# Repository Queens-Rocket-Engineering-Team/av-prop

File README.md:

# Propulsion Integration Systems
> 2025-2026 Season - Propulsion Integration Projects

> [!IMPORTANT]
> Make sure to initialize and pull the repository's git submodules to acquire all schematic library and board design dependencies:
> ```bash
> git submodule update --init --recursive
> ```

- Repository contains Avionics schematics, PCBs, and firmware for integrating with the propulsion stack.

### Folder Structure
- [`/Schematics`](./Schematics/) : Electrical design files (KiCad V8)  
- [`/Firmware`](./Firmware/) : C/C++ Code
- [`/Datasheets`](./Datasheets/) : Datasheets and reference materials  

### Documentation
- Boards and code are documented through `README` files in their respective directories. 

### Usage 
- To add or update features and work on new projects, create a new branch. 
- For **PCB** projects, name the branch with the convention: `pcb/board-name` or `pcb/board-feature` for updates.
- For **firmware** projects, name the branch with the convention: `fw/project-name` or `fw/project-feature` for updates.

--- 

QRET Avionics 25/26

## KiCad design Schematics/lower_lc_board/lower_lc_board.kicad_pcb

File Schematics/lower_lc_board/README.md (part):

# Lower Control Board (HYDRA) Documentation

<!--- removed left align div - weird github web issue --->
<details>
<summary><strong>Table of Contents</strong></summary>
  
- [Lower Control Board (HYDRA) Documentation](#lower-control-board-hydra-documentation)
  - [Overview](#overview)
    - [Key Features](#key-features)
  - [Circuit Design](#circuit-design)
    - [Power Management](#power-management)
      - [Power Entry](#power-entry)
      - [Power MUX](#power-mux)
      - [Power Switching](#power-switching)
    - [MCU Breakout](#mcu-breakout)
      - [Mode Selection](#mode-selection)
      - [Flash Storage Module](#flash-storage-module)
      - [CANBUS Interface](#canbus-interface)
      - [Serial Wire Debug](#serial-wire-debug)
      - [USB Interface](#usb-interface)
      - [System Feedback](#system-feedback)
    - [Valve Control](#valve-control)
    - [Sensing](#sensing)
      - [Data Acquisition](#data-acquisition)
      - [Pressure Transducers](#pressure-transducers)
      - [Thermocouples](#thermocouples)
  - [Board Design](#board-design)
    - [Physical Design Notes](#physical-design-notes)
    - [Electrical Characteristics](#electrical-characteristics)
    - [System Partitioning](#system-partitioning)
  - [Revision History](#revision-history)
  - [Contributors](#contributors)

</details>

---

## Overview

<div style="display: flex; gap: 10px;">

</div>

<em>Fig. 1: Hydra</em>

The **Lower LC/Hydra** board is a control board designed for integration with the rocket's propulsion system.
It operates in the **lower valve bay**, and drives solenoids to control the **dump** and **fill** valves.
This board supports analog pressure and temperature sensing, two digital hall-effect sensors for solenoid-status reading, and communication with the rest of the stack through CANbus.

Interfaces with:
- STM32F1 MCU
- Two 24V 205292 Solenoids
- Two 24V 4-20mA Pressure Transducers (PT)
- An Omega SA3-K Thermocouple (TC)
- Two TMAG273 digital hall-effect sensors (via breakout board)

### Key Features

- STM32F1 microcontroller with additional memory
- I2C and SPI interfaces for sensor integration
- Controlled power delivery for sensors and solenoids
- ORing circuits for power management
- Visual indication for status and debugging
- 4-layer PCB with dedicated ground planes
- Protection and filtering components across board

---

## Circuit Design

This board is primarily composed of four circuit modules representing its critical systems: [Power Management](#power-management), [STM32 Breakout](#mcu-breakout), [Valve Control](#valve-control), and [Sensing](#sensing).

All schematics are available as `kicad_sch` files in this directory.

---

### Power Management

This board receives power from the Hybrid Power Module through the Backplane.
For more information on power delivery, check out [this repository](https://github.com/Queens-Rocket-Engineering-Team/av-power).

The supply delivers **three** levels of voltage to the board:

| Voltage (V) | Purpose |
|-------------|---------|
| 3.3 | Logic supply for microcontroller and other peripheral devices; also serves as a reference for signal conditioning and protection circuits |
| 5 | Intermediate supply for specific peripheral devices |
| 24 | High-voltage supply for driving external devices such as solenoids and sensors |

> **Note:** 3.3V is referred to as **3V3** throughout this document.

#### Power Entry

Power rails enter through a Molex Micro-Fit connector and are conditioned by bulk filtering and input protection circuitry. These circuits apply to the 5V and 24V rails, each decoupled with 100 µF electrolytic capacitors to handle voltage transients and provide local energy storage. The 24V rail includes a 2A fuse for overcurrent protection.

Other power sources come from communication devices such as the USB connection and the JTAG debugger. The USB creates a voltage rail of 5V, which is then stepped down to 3V3 with a **Low-Dropout Regulator (LDO)**. The JTAG debugger supplies 3V3.

All rails feature test points and LEDs for diagnosis and debugging.

#### Power MUX

Power Multiplexers (MUX) are circuits that select between multiple power inputs to drive a single load. This is needed to avoid back-feeding between power sources, which could lead to unintended powering of interfaces and potential damage.

This implementation uses a **Triple OR-ing** circuit to select between three 3.3V inputs: Backplane (V_BP), JTAG (V_SWD), and USB (V_USB).

- The circuit involves three Ideal Diode ICs, which use a MOSFET and controller to mimic the behaviour of an **Ideal Diode** (zero voltage drop when forward-biased, zero current when reverse-biased).
- The logic follows:
  - **ON condition**: A chip turns on if its *Vin* is **higher** than the common output rail *Vout*.
  - Each chip uses its enable *CE* pin to monitor the output rail; if it sees a higher voltage present, it remains closed to prevent back-feeding.

In summary, a source will only drive the load if its voltage is higher than the current voltage on the output rail, allowing only **one** source to drive the output rail at a time.

- Capacitors are placed at the input pins to filter noise and prevent voltage spikes when a source is suddenly connected or disconnected.
- On the output rail, capacitors act as reservoirs to maintain steady voltage while also filtering noise generated by the loads connected to the 3V3 rail.

#### Power Switching

The delivery of 24V to the pressure transducers and solenoids is controlled through a switching circuit.

- For PTs, this was added to reduce power consumption by enabling sensor power only during active operation.
- For solenoids, this was added as a pre-actuation layer to provide additional protection and controlled switching.
- The controlled output rails are identified as `VPT` and `VSOL` respectively.

The circuit uses a **CMOS** (dual-MOSFET) setup: one N-channel at the input to drive a P-channel for the output.

**MOSFET Basics**

| Type | ON Condition |
|------|-------------|
| N-Channel | Gate voltage higher than source -> V<sub>GS</sub> > V<sub>th</sub> |
| P-Channel | Gate voltage lower than source -> V<sub>GS</sub> < V<sub>th</sub> |

The **ON** state connects the **Drain** (output) pin to the **Source** pin.

**Logic**

- The STM32 outputs a digital signal to drive the gate of the N-channel MOSFET. The source of the MOSFET is set to GND (0V).
- The gate is now at a higher voltage than the source, setting the drain to GND.
- The drain connects to a resistor divider with 24V to drive the gate of the P-channel MOSFET. The source of the MOSFET is set to 24V.
  - The resistor divider limits the gate voltage to approximately 14.81 V, lower than the source, setting the drain to 24V and powering the output rail.

$$V_g = 24 \times \frac{10k}{(6.2k + 10k)} \approx 14.81\ \text{V}$$

$$V_{gs} = 14.81 - 24 \approx -9.19\ \text{V}$$

> From the [DMP4065 Datasheet](${KIPRJMOD}/../../Datasheets/pMOSFET_DMP4065S-7_DS.pdf), V<sub>GS(max)</sub> = ±20 V, within safe operating range.

- `VPT` is filtered using a Pi filter with a ferrite bead between a 10 µF bulk capacitor and a 0.1 µF decoupling capacitor to reduce ripple and high-frequency noise.
- `VSOL` is decoupled with a 100 µF electrolytic capacitor for local energy storage and transient support.
- `VSOL` also uses a voltage divider for sensing. Two resistors (100 kΩ and 10 kΩ) scale the 24V input down to approx. 2.18V for measurement by an STM32 ADC input:

$$V = 24 \times \frac{10k}{(100k + 10k)} \approx 2.18\ \text{V}$$

The circuit also includes two resistors at the MOSFET gate:
- **Series (Gate) Resistor**: Limits inrush current into the gate while controlling switching speed and protecting the MCU pin.
- **Pull-Down Resistor**: Connects signal to GND to define a default logic state when nothing is actively driving the gate.

---

### MCU Breakout

The [STM32F103](https://www.st.com/resource/en/datasheet/stm32f103cb.pdf) was selected for this board's MCU.

Key features:
- 72 MHz ARM Cortex-M3 core
- Internal CAN controller
- Compact LQFP48 package

#### Mode Selection

The STM32 can be put into **BOOT** mode and **RESET** with onboard buttons.

**BOOT** mode determines whether the chip runs existing code from flash memory or waits to download new firmware.
- The STM32 reads the state of the BOOT pin (BOOT0) during reset to select the appropriate boot mode.
- It is **active-high**: when pulled HIGH (3V3), it will wait for new code over serial/USB.
- The circuit consists of a momentary push-button and a pull-down resistor to ensure the chip is disabled by default. A second BOOT pin (BOOT1) is pulled low to prevent entering SRAM mode.

**RESET** controls the Reset (NRST) pin --- the ON/OFF switch for the STM32.
- It is **active-low**: when pulled to GND the chip turns off; when released, it restarts.
- The circuit consists of a momentary push-button, a pull-up resistor to ensure the chip is enabled by default, and a 0.1 µF capacitor to filter out button noise (debouncing).

| BOOT0 Level | Boot Mode |
|-------------|-----------|
| HIGH | Programming Mode |
| LOW | Memory Mode |

#### Flash Storage Module

This board includes a BY25Q12BE5 SPI flash memory module providing 16 MB of external non-volatile storage, connected to the MCU via an SPI interface (SCLK, MOSI, MISO, CS).

#### CANBUS Interface

The STM32 includes an internal CAN controller but requires a CAN transceiver to interface with the stack's CANBUS.
- Differential pairs from the backplane edge connector are routed to the CAN transceiver, which converts them into TX and RX signals for the STM32.
- The CAN transceiver selected is a high-speed [TCAN1051](https://www.ti.com/lit/ds/symlink/tcan1051h.pdf).

#### Serial Wire Debug

This board supports Serial Wire Debug (SWD) for programming and debugging the MCU using an ST-Link debugger.
- The SWD interface uses dedicated SWDIO and SWCLK lines routed to a debug header.
- This enables flashing and debugging via an ST-Link programmer.

#### USB Interface

The STM32 interfaces with USB via a CP2102N USB-to-UART bridge.
- USB differential pairs are routed directly to the CP2102N, which converts them to UART signals for the STM32.
- The STM32 communicates with the bridge using standard TX and RX lines.

#### System Feedback

This board incorporates feedback through LEDs:
- Visual indicators include a DEBUG indicator, CAN status, and a general STATUS indicator.
- These consist of standard current-driven LEDs and an ARGB LED.

---

### Valve Control

Valves are actuated via solenoids using MOSFET-based switching circuits driven by the MCU.
- The system uses two Festo 205292 solenoids to control the rocket's dump and fill valves.
  - Operates at 24V and is active-low.
  - Controlled via low-side switching (active when pulled to ground).
  - Interfaces through a MOLEX Nano-Fit connector.

The circuits consist of an N-channel MOSFET for low-side switching, flyback (Schottky) diodes for protection, and hardware-driven LEDs for visual indication.

> See the **MOSFET Basics** section under [Power Management](#power-management) for background on MOSFET operation.

**Logic**

- The solenoid positive terminal is connected to 24V.
- The STM32 outputs a digital signal that serves as the circuit's control input.
- This signal feeds an N-channel MOSFET with its source connected to GND (0V) and its drain connected to the negative terminal of the solenoid (SOL_RET).
- The signal turns the MOSFET `ON` since the gate voltage (3.3V) is higher than the source voltage (0V).
- This connects the MOSFET drain to source, pulling the solenoid negative terminal to ground and actuating the valve.

**Protection & Filtering**

- A 40V, 3A SS34 Schottky diode is placed across the solenoid to provide a path for inductive flyback current during turn-off, protecting against voltage spikes generated by inductive loads during switching.
- A local 0.1 µF capacitor is placed near the connector for high-frequency decoupling.

**Visual Indication**

- A purely hardware-driven LED circuit provides indication and debugging.
  - An LED with a series current-limiting resistor is placed across the solenoid, with the anode on the positive terminal and the cathode on the negative terminal.
  - By default, the anode is connected to 24V and the cathode is floating.
  - When the solenoid is driven and the negative terminal is pulled low, the LED is connected on both sides and emits.

---

### Sensing

This board interfaces with several external sensors, including analog pressure transducers, thermocouples, and digital hall-effect sensors.
- Pressure transducers are used for analog telemetry measurements.
- Hall-effect sensors are used for solenoid state detection and feedback.

#### Data Acquisition

Analog sensor data is acquired via an external **ADC** (Analog-to-Digital Converter) through the SPI protocol. Digital signals from hall-effect sensors are acquired through the I2C protocol.

The ADC used is the [ADS131M04](https://www.ti.com/lit/ds/symlink/ads131m04.pdf): 8 input channels, 24-bit resolution, 32 kSPS programmable sampling rate.
- Each input channel receives a voltage or differential voltage from a sensor (V<sub>ref</sub> = 1.2 V).
- A [delta-sigma](https://e2e.ti.com/blogs_/archives/b/precisionhub/posts/delta-sigma-adc-basics-understanding-the-delta-sigma-modulator) modulator converts the voltage into a high-frequency bitstream representing the input analog signal. This modulator is driven by an external crystal oscillator (8.319 MHz).
- The bitstream is then filtered to produce a clean, high-resolution digital value.
- The ADC sends a 24-bit number representing the measured voltage to the MCU via SPI.

An **RC filter** is used at the ADC inputs as a low-pass filter to smooth out high-frequency noise. The capacitor charges and discharges through the resistor, smoothing fast transients so the ADC sees a stable voltage.

> **Brief Overview on Analog Signals:** Analog signals vary continuously, taking any value within a given range, unlike digital signals which have discrete levels. Changes in a sensor's physical quantity are represented proportionally as a voltage or current signal.

#### Pressure Transducers

The PT circuits are built around signal conditioning and protection before the ADC.
- The PT used is a 4-20 mA [Setra 209H](https://www.setra.com/hubfs/Setra_Product_Data_Sheets/Model_209H_Spec_Sheet_2016_PRELIMINARY_WATERMARK.pdf) connected via Molex Nano-Fit.
- The signal line is initially referenced to GND through a 62 Ω shunt resistor to produce a voltage drop proportionate to the signal (current):

$$R_{shunt} = \frac{V_{ref}}{I_{max}} = \frac{1.2\ \text{V}}{0.02\ \text{A}} = 60\ \Omega$$

> A 62 Ω resistor was chosen for availability.

- The signal is then clamped to 3.3V and GND using low-leakage diodes.
- A 1 kΩ resistor is placed in series between the signal and diode to limit current into the diodes during overvoltage conditions.
- The clamped signal then passes through a 200 Ω resistor and 10 nF capacitor, forming the RC low-pass filter before being sampled by the ADC.

#### Thermocouples

The TC circuits are built around signal conditioning, protection, and transformation before the ADC.
- The TC used is an [Omega SA3-L](https://assets.omega.com/pdf/test-and-measurement-equipment/temperature/sensors/thermocouple-probes/SA3.pdf) connected via screw terminal.
- Unlike the 4–20 mA pressure transducer, it produces a small differential voltage across its two output wires, so the device uses two signal inputs for differential measurement.
- Both signal lines are resistor-biased with two 1 MΩ resistors, connected to 3V3 and GND respectively, to establish a defined reference operating point and prevent floating inputs.
- The signals are then clamped to 3.3V and GND using low-leakage diodes.
- A 1 kΩ resistor is placed in series between each signal and diode to limit current during overvoltage conditions.
- Each signal then passes through a 200 Ω resistor and 10 nF capacitor, forming the RC low-pass filter before being sampled by the ADC.

**Cold-Junction Compensation**

Cold-junction compensation is used to determine the true absolute temperature at the TC connector, since a thermocouple only measures the temperature difference between the measurement junction and the reference junction.

- A **thermistor** placed as close as possible to the TC screw terminal measures the reference junction (PCB terminal) temperature.
- The thermistor uses a voltage divider to produce a proportional signal for processing by the STM32's internal ADC.

---

## Board Design

### Physical Design Notes

- The board measures 69.5 mm × 60 mm.
- Connectors are placed at the board edge for accessibility.
- The board outline deviates from the standard avionics form factor to fit the lower valve bay.
- A side-mounted Molex connector is used instead of the standard edge-connector (PCIe) connector for power and CAN entry due to space constraints.

### Electrical Characteristics

The board is a 4-layer PCB with dedicated ground planes for noise reduction and signal integrity.

| Layer | Net | Purpose |
|-------|-----|---------|
| 1 | Signals + Power | Top-level routing |
| 2 | GND | Inner ground plane |
| 3 | GND | Inner ground plane |
| 4 | Signals + Power | Bottom-level routing |

- Inner ground planes minimize impedance in return paths and reduce EMI.
- Decoupling capacitors are placed close to IC power pins to reduce loop inductance.
- Valve control circuits use local ground pours to support high-current return paths (MOSFET source).

### System Partitioning

- The board is partitioned into distinct analog, digital, and power domains to reduce noise coupling and improve signal integrity.
- Analog sensing circuitry is physically isolated from high-current valve control circuits.
- Power distribution is routed from the top of the board and propagates downward through regulated domains.
- High-current switching paths are separated from sensitive signal routing to minimize interference.

---

## Revision History

| Revision | Date | Description |
|----------|------|-------------|
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
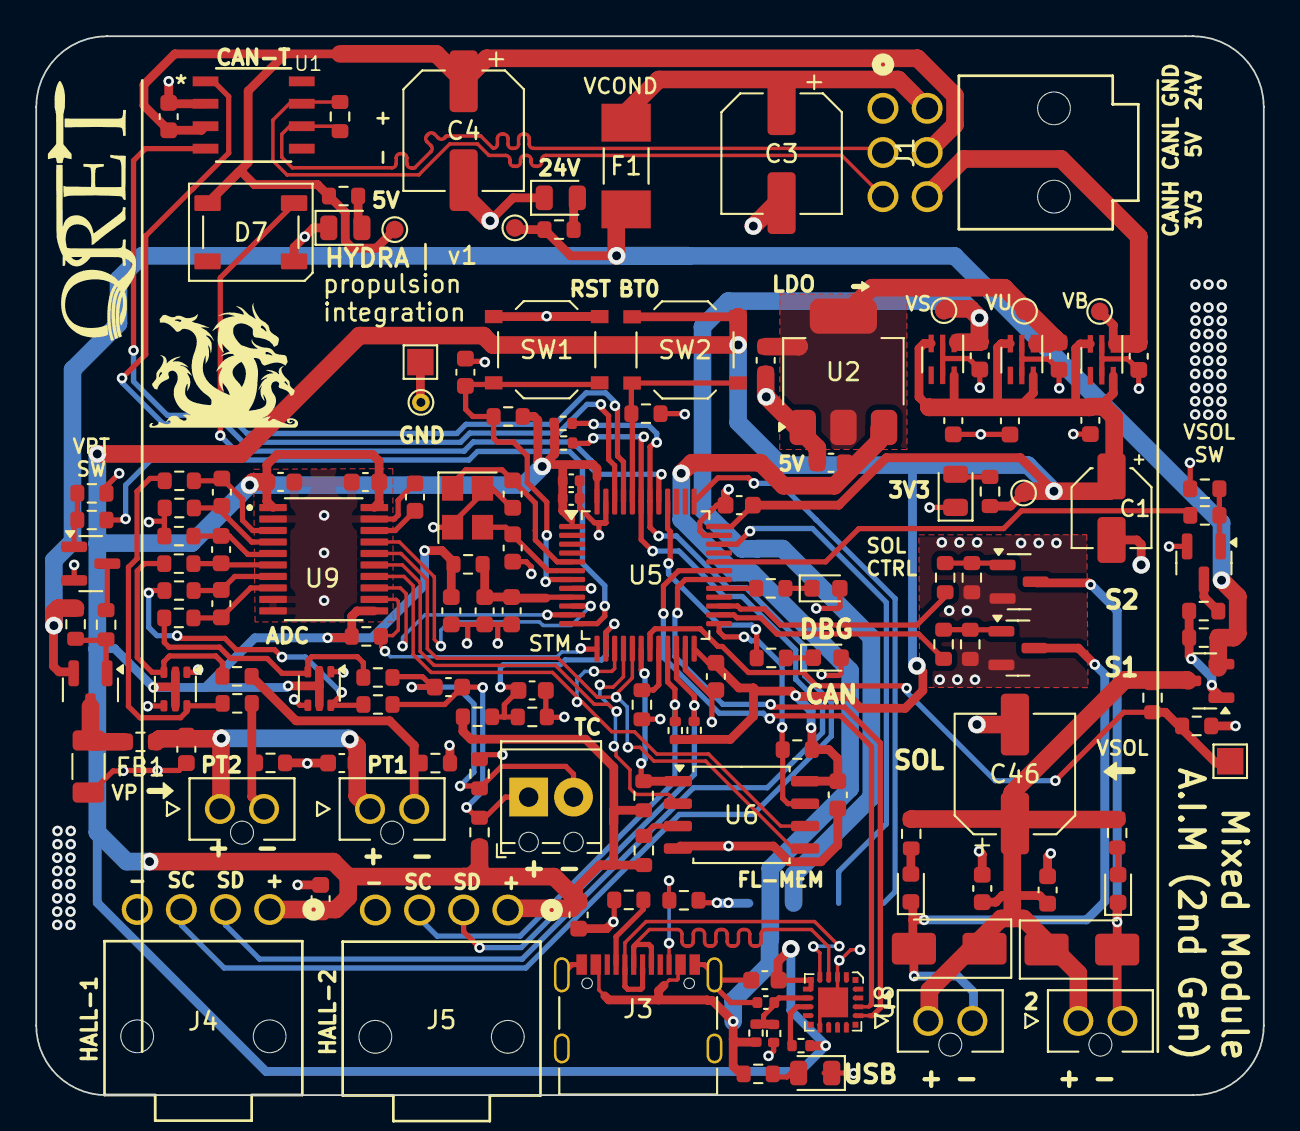
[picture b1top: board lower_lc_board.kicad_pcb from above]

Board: 4 copper layers, 69.5 x 60.0 mm, 149 parts (1 on the bottom side), 86 nets.

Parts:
C1: 10uF; CP_Elec_4x5.4
C2, C18, C23, C30, C33, C39, C41, C45, C52: 0.1uF; C_0603_1608Metric
C3, C4, C46: 100uF; CP_Elec_6.3x5.9
C5, C6, C28, C43, C44, C48, C49: 1uF; C_0603_1608Metric
C7, C12, C21, C50: 10uF; C_0603_1608Metric
C8, C9, C17: 100nF; C_0603_1608Metric
C10, C11: 10p; C_0603_1608Metric
C13, C14: 100n; C_0402_1005Metric
C15, C16: 100n; C_0603_1608Metric
C20: 1uF; C_0402_1005Metric
C26, C27, C34, C56: 10nF; C_0603_1608Metric
C29: 220 nF; C_0603_1608Metric
C35: 10uF; C_1206_3216Metric
C51: 1nF; C_0603_1608Metric
D1: PWR_3V3_LED (GRN); LED_0805_2012Metric
D2: PWR_24V_LED (GRN); LED_0805_2012Metric
D3: PWR_5V_LED (GRN); LED_0805_2012Metric
D4: USB_LED (GRN); LED_0805_2012Metric
D5: DB_LED (YLW); LED_0603_1608Metric
D6: CAN_LED (WHT); LED_0603_1608Metric
D7: SYS_LED; LED_WS2812B_PLCC4_5.0x5.0mm_P3.2mm
D11: SOL2_LED (YELW); LED_0603_1608Metric
D12: SOL1_LED (YELW); LED_0603_1608Metric
D13, D18: BAV199DW; SOT-363_SC-70-6
D15, D16: SS34; D_SMA
F1: Fuse; FUSC6125X279N
FB1, FB2: 600R; R_0603_1608Metric
J1: Conn_01x06; CONN_SD-105314-100_06_MOL
J2: SWD_CONN; SWD_PinHeader_1x04_P2.54mm_Horizontal_SMD
J3: USB_C_CONN; USB_C_DB-108PWB
J4: HALL-1; CONN_SD-105313-100_04_MOL
J5: HALL-2; CONN_SD-105313-100_04_MOL
J6, J8: PT; MOLEX_1053091102
J7: Screw_Terminal_01x02; TerminalBlock_Phoenix_MPT-0,5-2-2.54_1x02_P2.54mm_Horizontal
J9, J10: SOL_CONN; MOLEX_1053091102
Q1, Q2: AO3400A; SOT-23
Q3, Q5: 2N7002; SOT-23
R1: 3.3k; R_0603_1608Metric
R2, R30, R31: 12k; R_0603_1608Metric
R3, R16, R23, R51: 6.2k; R_0603_1608Metric
R5, R6, R7, R8, R22, R25, R43, R48, R49, R50, R52, R54, R60: 10k; R_0603_1608Metric
R9, R10: 5.1k; R_0603_1608Metric
R11: 22k; R_0402_1005Metric
R12: 47k; R_0402_1005Metric
R13: 1k; R_0402_1005Metric
R14: 680; R_0603_1608Metric
R15: 270; R_0603_1608Metric
R17, R18, R21, R45: 2.2k; R_0402_1005Metric
R19, R20: 1.2k; R_0603_1608Metric
R24, R28, R33, R37: 1k; R_0603_1608Metric
R26, R27: 1M; R_0603_1608Metric
R29, R34, R36, R38, R40, R41, R44, R53: 200; R_0603_1608Metric
R32, R35: 62; R_0603_1608Metric
R39, R42, R47: 100k; R_0603_1608Metric
R46: 120; R_0603_1608Metric
SW1: SW_STM_RESET; SW_Push_1P1T_XKB_TS-1187A
SW2: SW_STM_BOOT_MODE; SW_Push_1P1T_XKB_TS-1187A
TH1: Thermistor; R_0603_1608Metric
TP1: 24V-TP; TestPoint_Pad_D1.0mm
TP2: 3V3-TP; TestPoint_Pad_D1.0mm
TP3: GND-TP-H; TestPoint_THTPad_D1.0mm_Drill0.5mm
TP4: 3V3_BP; TestPoint_Pad_D1.0mm
TP5: GND-TP-P; TestPoint_Pad_1.5x1.5mm
TP6: 3V3_USB; TestPoint_Pad_D1.0mm
TP7: VSOL.S; TestPoint_Pad_1.5x1.5mm
TP9: V_SWD_TP; TestPoint_Pad_D1.0mm
TP13: 5V-TP; TestPoint_Pad_D1.0mm
U1: TCAN1051HGVDR; SOIC_1044BDR_TEX
U2: AMS1117-3.3; SOT-223-3_TabPin2
U3, U4, U10: ID_LM66100DCKR; SC-70-6
U5: STM32F103CBT6; LQFP-48_7x7mm_P0.5mm
U6: BY25Q128ES; SOIC-8_5.23x5.23mm_P1.27mm
U8: CP2102N-Axx-xQFN20; QFN-20-1EP_3x3mm
U9: ADC_ADS131M04IPWR; SOP65P640X120-20N
U11, U12: DMP4065S-7; SOT-23
Y1: X322516MMB4SI; Crystal_SMD_3225-4Pin_3.2x2.5mm

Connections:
5V_USB: C7.1, J3.A4 (VBUS), J3.A9 (VBUS), J3.B4 (VBUS), J3.B9 (VBUS), R11.2, R16.1, U2.3 (VI)
+3.3VA: C45.2, C48.2, FB2.1, U5.9 (VDDA)
+3V3: C1.1, C13.1, C14.1, C15.1, C16.1, C17.1, C21.2, C23.1, C28.2, C30.2, C33.1, C43.2, C49.1, C50.1, C51.1, C52.1, D13.2 (K2), D13.5 (K4), D18.2 (K2), D18.5 (K4), FB2.2, J4.1, J5.1, J7.1, R1.1, R6.2, R7.2, R8.2, R13.2, R17.2, R18.1, R21.2, R24.2, R25.2, R26.1, R26.2, R45.1, R48.1, R49.2, SW2.2, TP2.1, U3.3 (*CE), U3.6 (VOUT), U4.3 (*CE), U4.6 (VOUT), U5.1 (VBAT), U5.24 (VDD), U5.36 (VDD), U5.48 (VDD), U6.8 (VCC), U8.6 (VDD), U8.7 (VREGIN), U9.1 (AVDD), U9.11 (~SYNC/~RESET), U9.20 (DVDD), U10.3 (*CE), U10.6 (VOUT)
+5V: C4.1, C9.2, D7.1 (VDD), J1.5, R3.2, TP13.1, U1.3 (VCC)
+24V: F1.1, R2.2, R23.2, R51.2, TP1.1, U11.2 (S), U12.2 (S)
+24V_BP: C3.1, F1.2, J1.4
/Power Circuitry/3V3_BP: C5.2, J1.6, TP4.1, U3.1 (VIN)
/Power Circuitry/3V3_USB: C6.1, C12.1, TP6.1, U2.2 (VO), U4.1 (VIN)
/Sensing Circuitry/PT1_CLAMPED: C26.2, R34.1, U9.3 (AIN0P)
/Sensing Circuitry/PT2_CLAMPED: C27.2, R38.1, U9.6 (AIN1P)
/Sensing Circuitry/TC_N_1: C30.1, J7.2, R27.1, R28.2
/Sensing Circuitry/TC_N_CLAMPED_1: C56.1, R40.2, U9.8 (AIN2N)
/Sensing Circuitry/TC_P_CLAMPED_1: C56.2, R29.2, U9.7 (AIN2P)
/Valve Control Circuitry/VSOL: C39.1, C41.1, C46.1, D15.1 (K), D16.1 (K), J9.1, J10.1, R30.2, R31.2, R47.1, U12.3 (D)
ADC_CLKIN: U5.10 (PA0), U9.17 (CLKIN)
ADC_CS: R49.1, U5.13 (PA3), U9.12 (~CS)
ADC_DRDY: U5.11 (PA1), U9.13 (~DRDY)
BOOT0: R5.2, SW2.1, U5.44 (BOOT0)
BOOT1: R60.2, U5.20 (PB2)
CAN_LED: R15.1, U5.40 (PB4)
CAN_N: J1.2, R46.1, U1.6 (CANL)
CAN_P: J1.3, R46.2, U1.7 (CANH)
CAN_RX: U1.4 (RXD), U5.45 (PB8)
CAN_TX: U1.1 (TXD), U5.46 (PB9)
CJC_SENSE: C34.2, R25.1, TH1.1, U5.14 (PA4)
DB_LED: R14.1, U5.29 (PA8)
FL_CS: R48.2, U5.18 (PB0), U6.1 (~CS)
GND: C1.2, C2.2, C3.2, C4.2, C5.1, C6.2, C7.2, C8.2, C9.1, C10.2, C11.2, C12.2, C13.2, C14.2, C15.2, C16.2, C17.2, C18.2, C20.1, C21.1, C23.2, C28.1, C29.2, C33.2, C34.1, C35.2, C39.2, C41.2, C43.1, C44.2, C45.1, C46.2, C48.1, C49.2, C50.2, C51.2, C52.2, D1.1 (K), D2.1 (K), D3.1 (K), D4.1 (K), D5.2 (A), D6.2 (A), D7.3 (VSS), D13.1 (A1), D13.4 (A3), D18.1 (A1), D18.4 (A3), J1.1, J2.1 (GND), J3.A1 (GND), J3.A12 (GND), J3.B1 (GND), J3.B12 (GND), J3.S1 (SHIELD), J4.4, J5.4, Q1.2 (S), Q2.2 (S), Q3.2 (S), Q5.2 (S), R5.1, R9.2, R10.2, R12.1, R19.1, R20.1, R27.2, R32.1, R35.1, R39.1, R42.1, R43.1, R52.1, R54.1, R60.1, SW1.1, TH1.2, TP3.1, TP5.1, U1.2 (GND), U2.1 (ADJ), U3.2 (GND), U3.5 (ST), U4.2 (GND), U4.5 (ST), U5.8 (VSSA), U5.23 (VSS), U5.35 (VSS), U5.47 (VSS), U6.4 (GND), U8.3 (GND), U8.12 (GND), U8.21 (GND), U9.2 (AGND), U9.9 (AIN3N), U9.10 (AIN3P), U9.19 (DGND), U10.2 (GND), U10.5 (ST), Y1.2, Y1.4
HALL_SCL1: J4.3, R18.2, U5.42 (PB6)
HALL_SCL2: J5.3, R45.2, U5.21 (PB10)
HALL_SDA1: J4.2, R17.1, U5.43 (PB7)
HALL_SDA2: J5.2, R21.1, U5.22 (PB11)
unnamed: D1.2 (A), R1.2
unnamed: D2.2 (A), R2.1
unnamed: D3.2 (A), R3.1
unnamed: D4.2 (A), R16.2
unnamed: D5.1 (K), R14.2
unnamed: D6.1 (K), R15.2
unnamed: D11.2 (A), R30.1
unnamed: D12.2 (A), R31.1
unnamed: D13.6 (K3A4), R33.2, R34.2
unnamed: D13.3 (K1A2), R37.2, R38.2
unnamed: D18.6 (K3A4), R24.1, R29.1
unnamed: D18.3 (K1A2), R28.1, R40.1
unnamed: J3.A5 (CC1), R9.1
unnamed: J3.B5 (CC2), R10.1
unnamed: J6.2, R32.2, R33.1
unnamed: J8.2, R35.2, R37.1
unnamed: Q1.1 (G), R36.1, R39.2
unnamed: Q2.1 (G), R41.1, R42.2
unnamed: Q3.3 (D), R22.1
unnamed: Q3.1 (G), R43.2, R44.2
unnamed: Q5.3 (D), R50.1
unnamed: Q5.1 (G), R52.2, R53.2
unnamed: R8.1, U6.3 (IO2)
unnamed: C20.2, R11.1, R12.2, U8.8 (VBUS)
unnamed: R13.1, U8.9 (~RST)
unnamed: C26.1, R19.2, U9.4 (AIN0N)
unnamed: C27.1, R20.2, U9.5 (AIN1N)
unnamed: C29.1, U9.18 (CAP)
unnamed: C35.1, FB1.2, U11.3 (D)
unnamed: R22.2, R23.1, U11.1 (G)
unnamed: R50.2, R51.1, U12.1 (G)
OSC_IN: C10.1, U5.5 (PD0), Y1.1
OSC_OUT: C11.1, U5.6 (PD1), Y1.3
RESET_FL: R7.1, U5.25 (PB12), U6.7 (IO3)
RGB_DATA: D7.4 (DIN), U5.41 (PB5)
SOL1_EN: R36.2, U5.26 (PB13)
SOL1_RET: D12.1 (K), D16.2 (A), J10.2, Q1.3 (D)
SOL2_EN: R41.2, U5.27 (PB14)
SOL2_RET: D11.1 (K), D15.2 (A), J9.2, Q2.3 (D)
SPI_MISO: U5.16 (PA6), U6.2 (DO(IO1)), U9.15 (DOUT)
SPI_MOSI: U5.17 (PA7), U6.5 (DI(IO0)), U9.16 (DIN)
SPI_SCLK: U5.15 (PA5), U6.6 (CLK), U9.14 (SCLK)
STM_RESET: C8.1, R6.1, SW1.2, U5.7 (NRST)
SWCLK: J2.4 (SWCLK), U5.37 (PA14)
SWDIO: J2.3 (SWDIO), U5.34 (PA13)
USART_RX: U5.31 (PA10), U8.18 (TXD)
USART_TX: U5.30 (PA9), U8.17 (RXD)
USB_N: J3.A7 (D-), J3.B7 (D-), U8.5 (D-)
USB_P: J3.A6 (D+), J3.B6 (D+), U8.4 (D+)
VPT: C2.1, C18.1, FB1.1, J6.1, J8.1
VPT_EN: R44.1, U5.12 (PA2)
VSOL_EN: R53.1, U5.32 (PA11)
VSOL_SENSE: R47.2, R54.2, TP7.1, U5.19 (PB1)
V_SWD: C44.1, J2.2 (3V3), TP9.1, U10.1 (VIN)

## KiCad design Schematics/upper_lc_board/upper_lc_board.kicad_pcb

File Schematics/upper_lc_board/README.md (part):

# Upper Control Board (PEGASUS) Documentation

<!--- removed left align div - weird github web issue --->
<details>
<summary><strong>Table of Contents</strong></summary>

- [Upper Control Board (PEGASUS) Documentation](#upper-control-board-pegasus-documentation)
  - [Overview](#overview)
    - [Key Features](#key-features)
  - [Circuit Design](#circuit-design)
    - [Power Management](#power-management)
      - [Power Entry](#power-entry)
      - [Power MUX](#power-mux)
      - [Power Switching](#power-switching)
    - [MCU Breakout](#mcu-breakout)
      - [Mode Selection](#mode-selection)
      - [CANBUS Interface](#canbus-interface)
      - [USB Interface](#usb-interface)
      - [System Feedback](#system-feedback)
    - [Valve Control](#valve-control)
    - [Sensing](#sensing)
      - [Data Acquisition](#data-acquisition)
      - [Pressure Transducers](#pressure-transducers)
  - [Board Design](#board-design)
    - [Physical Design Notes](#physical-design-notes)
    - [Electrical Characteristics](#electrical-characteristics)
    - [System Partitioning](#system-partitioning)
  - [Revision History](#revision-history)
  - [Contributors](#contributors)

</details>

---

## Overview

<em>Fig. 1: Pegasus</em>

The **Upper LC/Pegasus** board is a control board designed for integration with the rocket's propulsion system.
It operates in the **upper valve bay**, and drives a solenoid to control the rocket's vent valve.
This board supports analog pressure sensing, a digital hall-effect sensor for solenoid-status reading, and communication with the rest of the stack through CANbus. It is also **WiFi-capable**.

Interfaces with:
- ESP32-S3 Module
- Two 24V 205292 Solenoids
- Two 24V 4-20mA Pressure Transducers (PT)
- One TMAG273 digital hall-effect sensor (via breakout board)

### Key Features

- ESP32-S3 microcontroller with integrated WiFi
- I2C and SPI interfaces for sensor integration
- Controlled power delivery for sensors
- ORing circuits for power management
- Auditory and visual indication for status and debugging
- 4-layer PCB with dedicated ground planes
- Protection and filtering components across board

---

## Circuit Design

---

### Power Management

This board receives power from the Hybrid Power Module through the Backplane.
For more information on power delivery, check out [this repository](https://github.com/Queens-Rocket-Engineering-Team/av-power).

The supply delivers **three** levels of voltage to the board:

| Voltage (V) | Purpose |
|-------------|---------|
| 3.3 | Logic supply for microcontroller and other peripheral devices; also serves as a reference for signal conditioning and protection circuits |
| 5 | Intermediate supply for specific peripheral devices |
| 24 | High-voltage supply for driving external devices such as solenoids and sensors |

> **Note:** 3.3V is referred to as **3V3** throughout this document.

#### Power Entry

Power rails enter through a PCIe connector (Stack Edge Connector) and are conditioned by bulk filtering and input protection circuitry. These circuits apply to the 5V and 24V rails, each decoupled with 100 µF electrolytic capacitors to handle voltage transients and provide local energy storage. The 24V rail includes a 2A fuse for overcurrent protection.

Other power sources come from communication devices such as the USB connection, creating a voltage rail of 5V, which is then stepped down to 3V3 with a **Low-Dropout Regulator (LDO)**.

All rails feature test points and LEDs for diagnosis and debugging.

Additionally, the 24V rail uses a voltage divider for sensing. Two resistors (100 kΩ and 10 kΩ) scale the 24V input down to approx. 2.18V for measurement by an ESP32 ADC input:

$$V = 24 \times \frac{10k}{(100k + 10k)} \approx 2.18\ \text{V}$$

#### Power MUX

Power Multiplexers (MUX) are circuits that select between multiple power inputs to drive a single load. This is needed to avoid back-feeding between power sources, which could lead to unintended powering of interfaces and potential damage.

This implementation uses a **Dual OR-ing** circuit to select between two 3.3V inputs: Backplane (V_BP) and USB (V_USB).

- The circuit involves two Ideal Diode ICs, which use a MOSFET and controller to mimic the behaviour of an **Ideal Diode** (zero voltage drop when forward-biased, zero current when reverse-biased).
- The logic follows:
  - **ON condition**: A chip turns on if its V<sub>in</sub> is **higher** than the common output rail V<sub>out</sub>.
  - Each chip uses its enable *CE* pin to monitor the output rail -- if it sees a higher voltage present, it remains closed to prevent back-feeding.

In summary, a source will only drive the load if its voltage is higher than the current voltage on the output rail, allowing only **one** source to drive the output rail at a time.

- Capacitors are placed at the input pins to filter noise and prevent voltage spikes when a source is suddenly connected or disconnected.
- On the output rail, capacitors act as reservoirs to maintain steady voltage while also filtering noise generated by the loads connected to the 3V3 rail.

#### Power Switching

The delivery of 24V to the pressure transducers is controlled through a switching circuit.
- This was added to reduce power consumption by enabling sensor power only during active operation.
- The controlled output rail is identified as `VPT`.

The circuit uses a **CMOS** (dual-MOSFET) setup: one N-channel at the input to drive a P-channel for the output.

**MOSFET Basics**

| Type | ON Condition |
|------|-------------|
| N-Channel | Gate voltage higher than source -- V<sub>GS</sub> > V<sub>th</sub> |
| P-Channel | Gate voltage lower than source -- V<sub>GS</sub> < V<sub>th</sub> |

The **ON** state connects the **Drain** (output) pin to the **Source** pin.

**Logic**

- The ESP32 outputs a digital signal `VPT-SW` to drive the gate of the N-channel MOSFET. The source of the MOSFET is set to GND (0V).
- The gate is now at a higher voltage than the source, setting the drain to GND.
- The drain connects to a resistor divider with 24V to drive the gate of the P-channel MOSFET. The source of the MOSFET is set to 24V.
  - The resistor divider limits the gate voltage to approximately 14.81 V, lower than the source, setting the drain to 24V and powering the `VPT` rail.

$$V_g = 24 \times \frac{10k}{(6.2k + 10k)} \approx 14.81\ \text{V}$$

$$V_{gs} = 14.81 - 24 \approx -9.19\ \text{V}$$

> From the [DMP4065 Datasheet](${KIPRJMOD}/../../Datasheets/pMOSFET_DMP4065S-7_DS.pdf), V<sub>GS(max)</sub> = ±20 V -- within safe operating range.

- VPT is filtered with a Pi filter, featuring a ferrite bead between a 10 µF bulk capacitor and a 0.1 µF high-frequency decoupling capacitor to suppress both low-frequency ripple and high-frequency noise.

The circuit also includes two resistors at the MOSFET gate:
- **Series (Gate) Resistor**: Limits inrush current into the gate while controlling switching speed and protecting the MCU pin.
- **Pull-Down Resistor**: Connects signal to GND to define a default logic state when nothing is actively driving the gate.

---

### MCU Breakout

The [ESP32-S3](https://documentation.espressif.com/esp32-s3_datasheet_en.pdf) module was selected for this board's MCU.

Key features:
- Integrated 2.4 GHz WiFi
- Native USB Serial/JTAG controller
- Internal CAN controller (TWAI)
- Flexible GPIO matrix

#### Mode Selection

The S3 can be put into **BOOT** mode and **RESET** with onboard buttons.

**BOOT** mode determines whether the chip runs existing code from flash memory or waits to download new firmware.
- The ESP32 reads the state of the BOOT pin (IO0) during reset to select the appropriate boot mode.
- It is **active-low**: when pulled to GND, it will wait for new code over serial/USB.
- The circuit consists of a momentary push-button and a 0.1 µF capacitor to filter out button noise (debouncing).

**RESET** controls the Enable (EN) pin which is the ON/OFF (reset) switch for the ESP32.
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
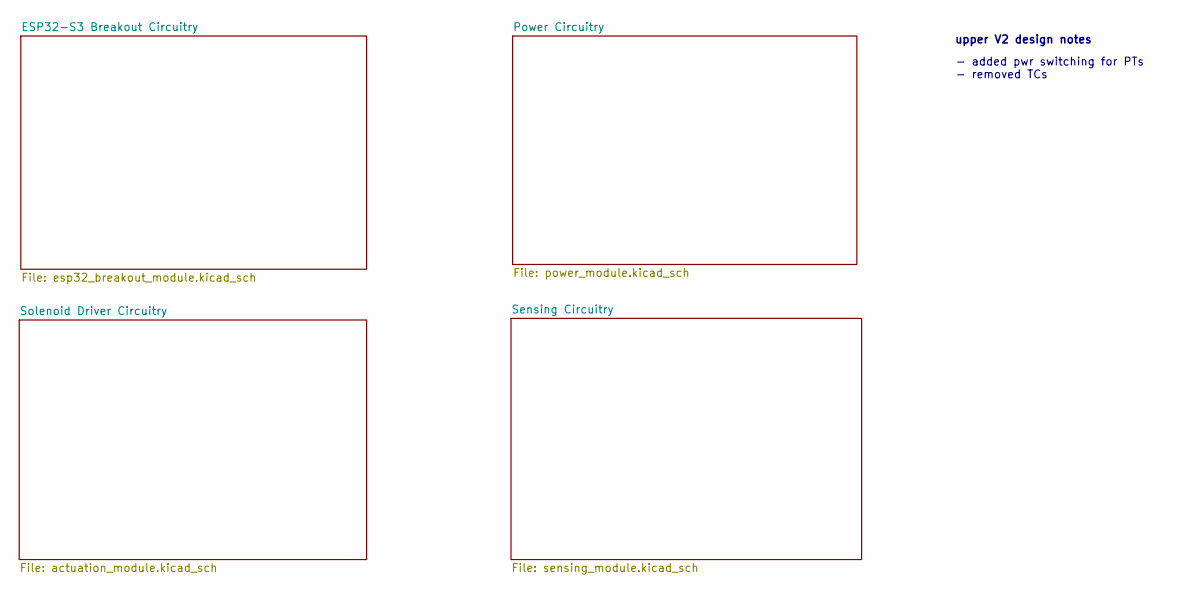
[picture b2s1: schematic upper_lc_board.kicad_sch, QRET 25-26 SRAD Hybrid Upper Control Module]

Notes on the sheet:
- added pwr switching for PTs - removed TCs
upper V2 design notes

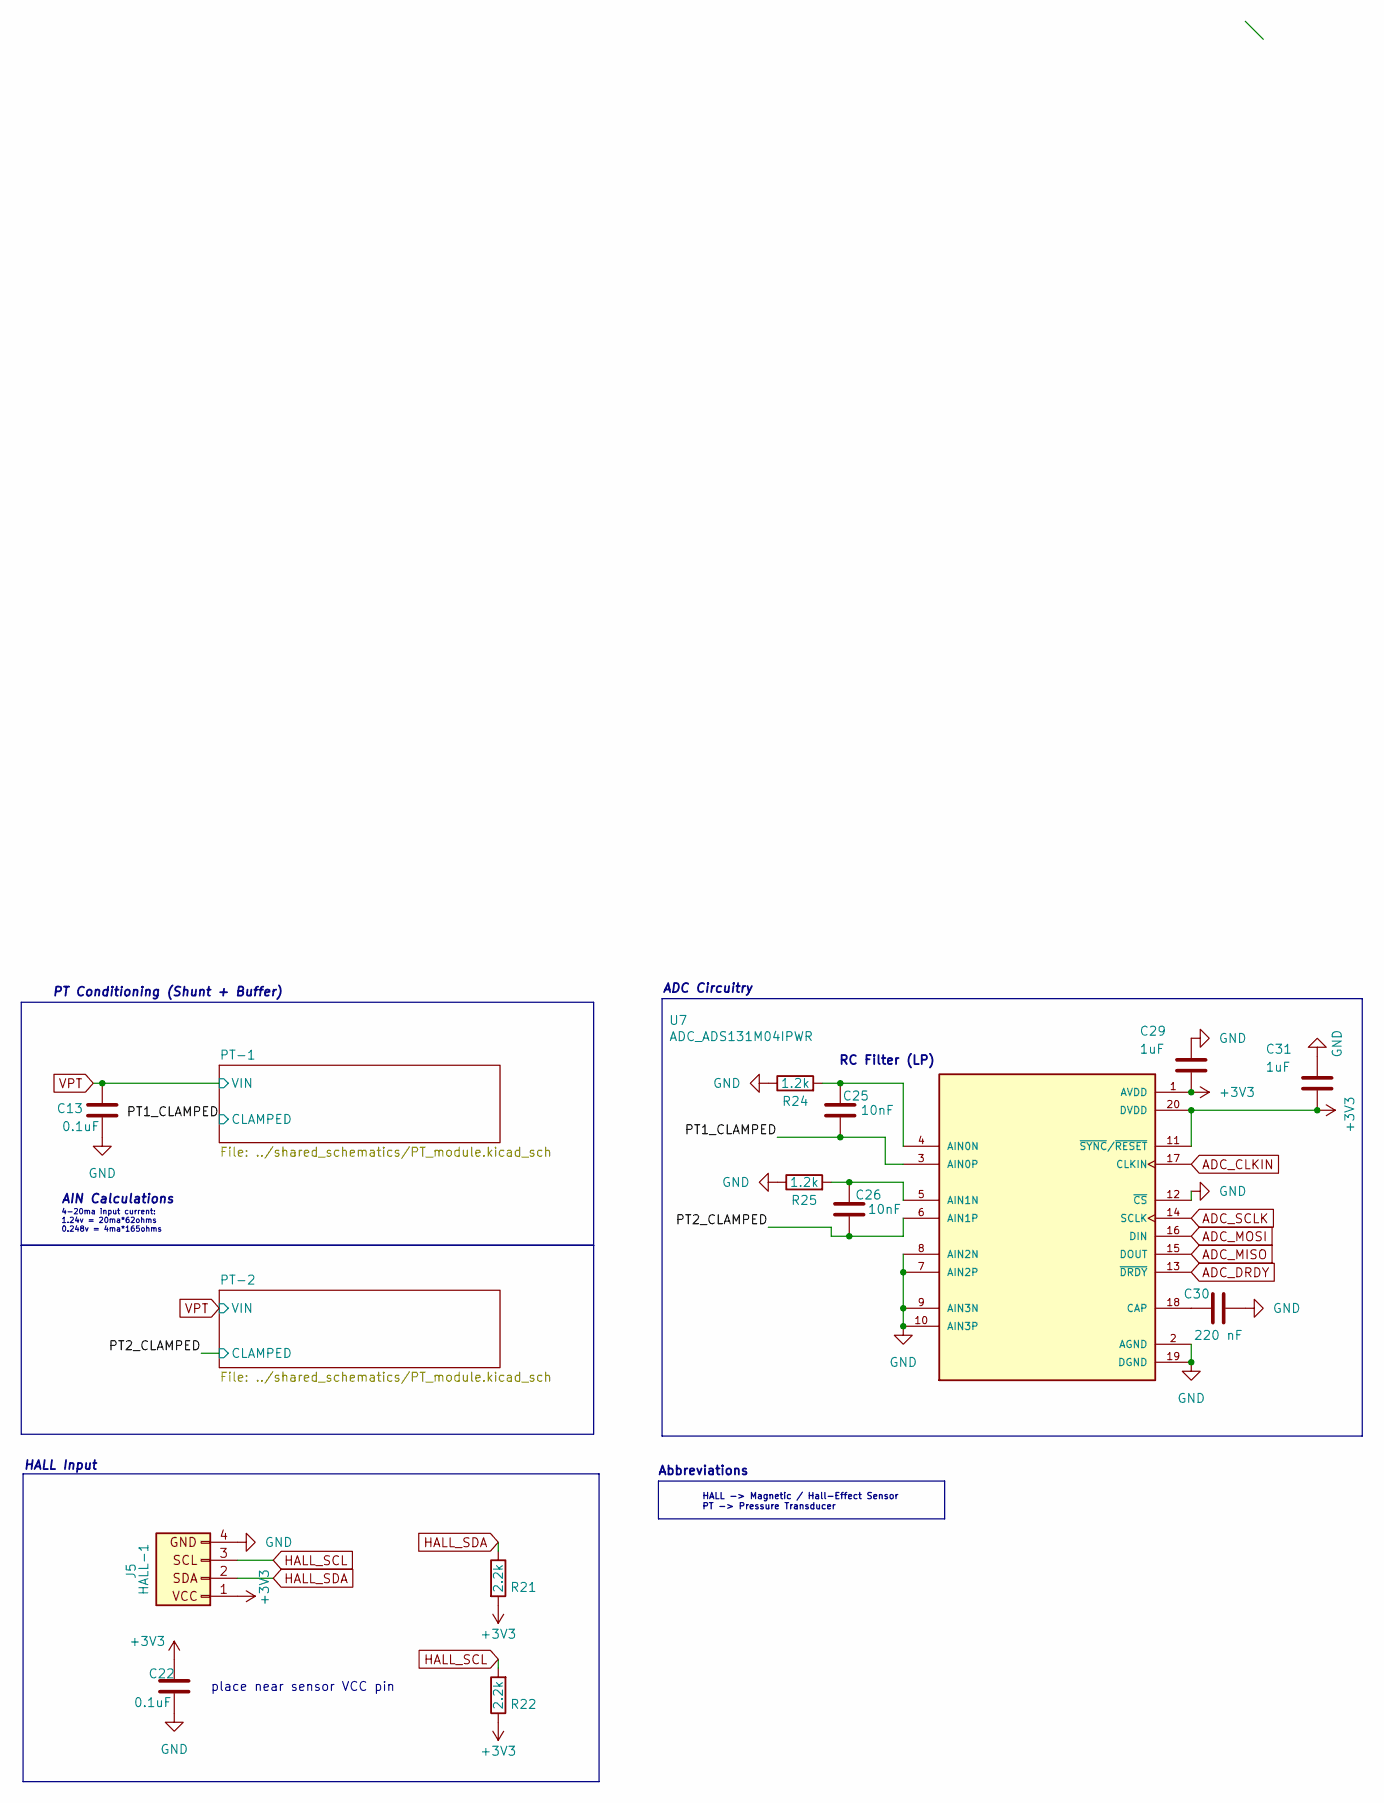
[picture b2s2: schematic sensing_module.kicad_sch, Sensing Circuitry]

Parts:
C13, C22: 0.1uF; C_0603_1608Metric; LCSC C14663
C25, C26: 10nF; C_0603_1608Metric; LCSC C57112
C29, C31: 1uF; C_0603_1608Metric; LCSC C15849
C30: 220 nF; C_0603_1608Metric; LCSC C21120
J5: HALL-1; CONN_SD-105313-100_04_MOL; Digikey WM16895-ND
R21, R22: 2.2k; R_0603_1608Metric; LCSC C4190
R24, R25: 1.2k; R_0603_1608Metric; LCSC C22765
U7: ADC_ADS131M04IPWR; SOP65P640X120-20N; PARTREV D; LCSC C2862562

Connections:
+3V3: C22.1, C29.2, C31.2, J5.1, R21.2, R22.1, U7.1 (AVDD), U7.11 (~SYNC/~RESET), U7.20 (DVDD); also elsewhere on the board
/Sensing Circuitry/PT1_CLAMPED: C25.2, U7.3 (AIN0P); also elsewhere on the board
/Sensing Circuitry/PT2_CLAMPED: C26.2, U7.6 (AIN1P); also elsewhere on the board
ADC_CLKIN: U7.17 (CLKIN); also elsewhere on the board
ADC_DRDY: U7.13 (~DRDY); also elsewhere on the board
ADC_MISO: U7.15 (DOUT); also elsewhere on the board
ADC_MOSI: U7.16 (DIN); also elsewhere on the board
ADC_SCLK: U7.14 (SCLK); also elsewhere on the board
GND: C13.2, C22.2, C29.1, C30.2, C31.1, J5.4, R24.1, R25.1, U7.2 (AGND), U7.7 (AIN2P), U7.8 (AIN2N), U7.9 (AIN3N), U7.10 (AIN3P), U7.12 (~CS), U7.19 (DGND); also elsewhere on the board
HALL_SCL: J5.3, R22.2; also elsewhere on the board
HALL_SDA: J5.2, R21.1; also elsewhere on the board
unnamed: C25.1, R24.2, U7.4 (AIN0N)
unnamed: C26.1, R25.2, U7.5 (AIN1N)
unnamed: C30.1, U7.18 (CAP)
VPT: C13.1; also elsewhere on the board

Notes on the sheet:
4-20ma input current: 1.24v = 20ma*62ohms 0.248v = 4ma*165ohms
HALL -> Magnetic / Hall-Effect Sensor PT -> Pressure Transducer
place near sensor VCC pin
ADC Circuitry
AIN Calculations
RC Filter (LP)
HALL Input
PT Conditioning (Shunt + Buffer)
Abbreviations

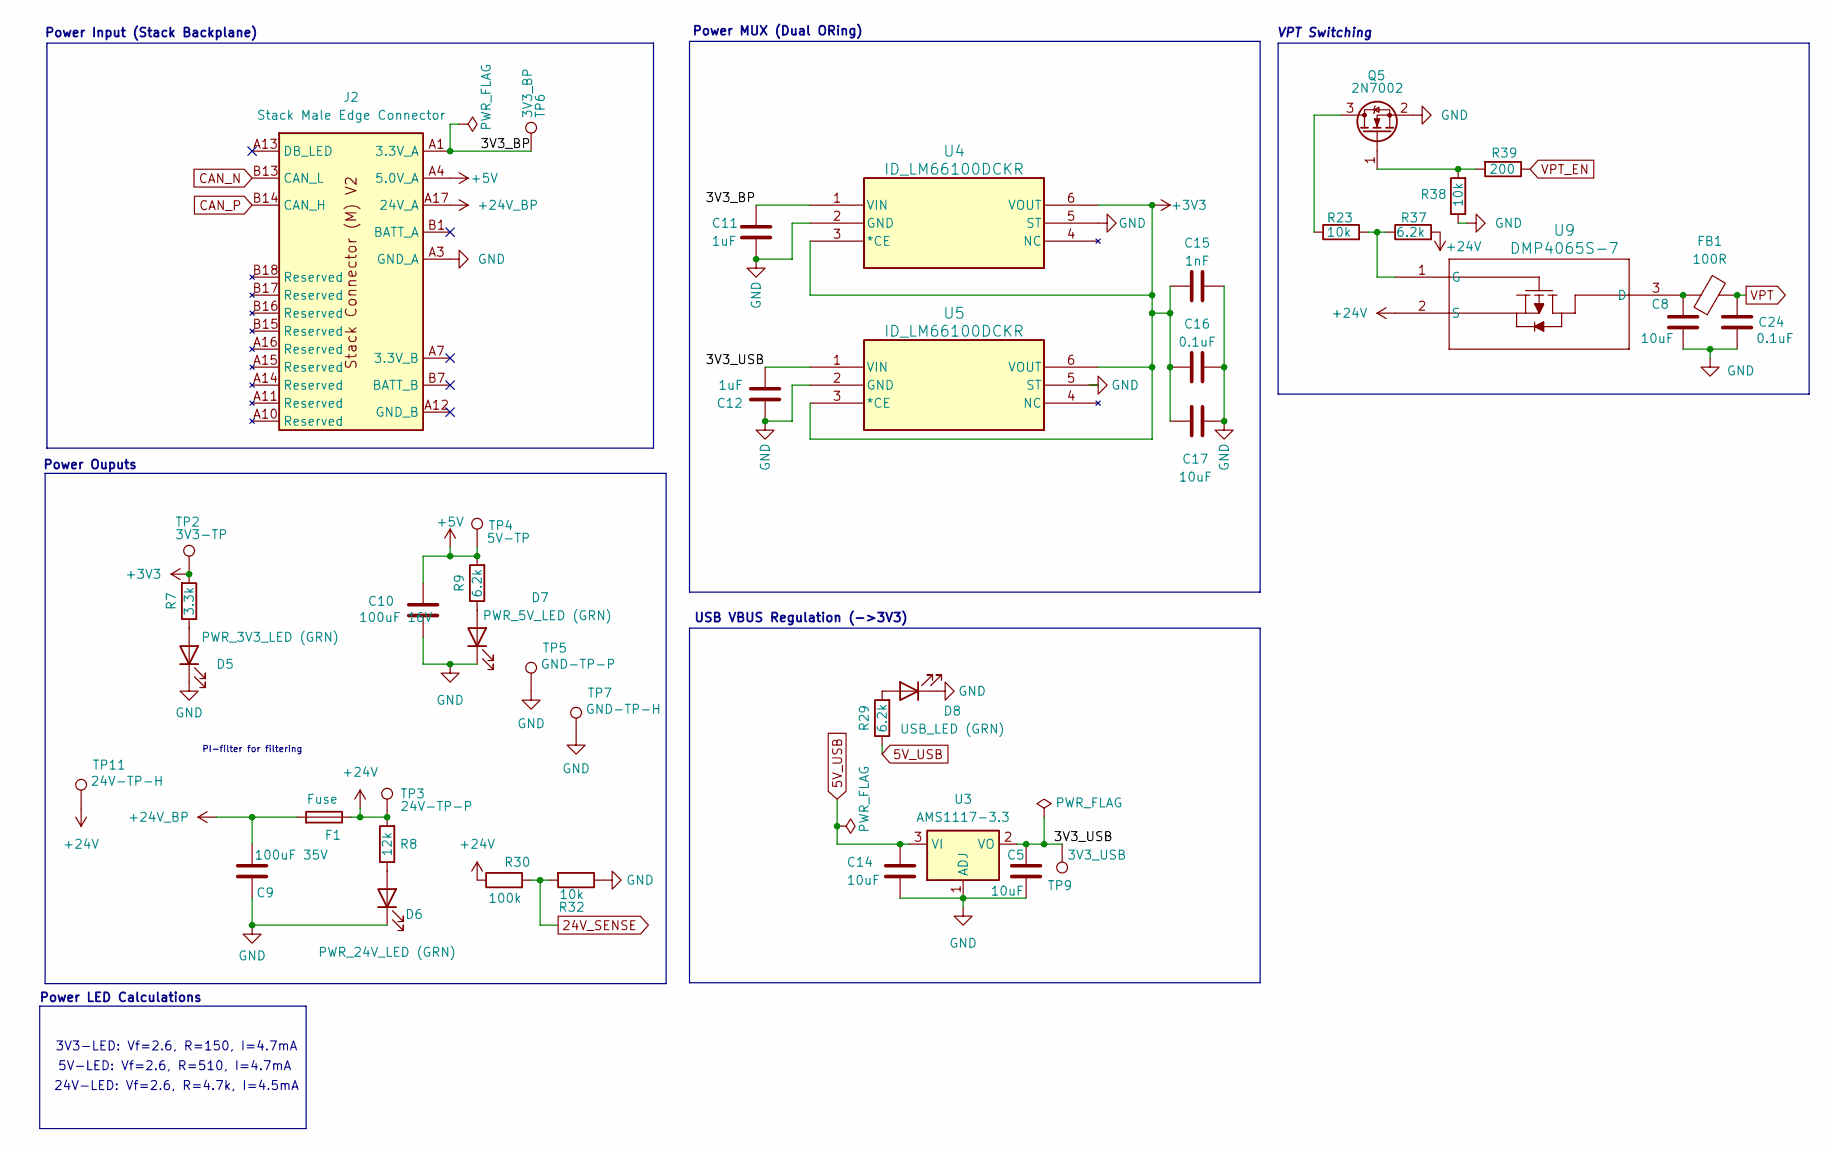
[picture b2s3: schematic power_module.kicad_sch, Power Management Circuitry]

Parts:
C5, C8, C14, C17: 10uF; C_0603_1608Metric; LCSC C96446
C9: 100uF 35V; CP_Elec_6.3x5.9; Digikey 732-8511-1-ND
C10: 100uF 16V; CP_Elec_6.3x5.9; Digikey 732-8419-1-ND
C11, C12: 1uF; C_0603_1608Metric; LCSC C15849
C15: 1nF; C_0603_1608Metric; LCSC C1588
C16, C24: 0.1uF; C_0603_1608Metric; LCSC C14663
D5: PWR_3V3_LED (GRN); LED_0805_2012Metric; LCSC C2297
D6: PWR_24V_LED (GRN); LED_0805_2012Metric; LCSC C2297
D7: PWR_5V_LED (GRN); LED_0805_2012Metric; LCSC C2297
D8: USB_LED (GRN); LED_0805_2012Metric; LCSC C2297
F1: Fuse; FUSC6125X279N; Digikey 5923-0679H2000-05CT-ND
FB1: 100R; R_0805_2012Metric; LCSC C1015
J2: Stack Male Edge Connector; BUS_PCIexpress_x1
Q5: 2N7002; SOT-23; LCSC C8545
R7: 3.3k; R_0603_1608Metric; LCSC C22978
R8: 12k; R_0603_1608Metric; LCSC C22790
R9, R29, R37: 6.2k; R_0603_1608Metric; LCSC C4260
R23, R32, R38: 10k; R_0603_1608Metric; LCSC C25804
R30: 100k; R_0603_1608Metric; LCSC C25803
R39: 200; R_0603_1608Metric; LCSC C8218
TP2: 3V3-TP; TestPoint_Pad_D1.0mm
TP3: 24V-TP-P; TestPoint_Pad_1.5x1.5mm
TP4: 5V-TP; TestPoint_Pad_D1.0mm
TP5: GND-TP-P; TestPoint_Pad_1.5x1.5mm
TP6: 3V3_BP; TestPoint_Pad_D1.0mm
TP7: GND-TP-H; TestPoint_THTPad_D1.0mm_Drill0.5mm
TP9: 3V3_USB; TestPoint_Pad_D1.0mm
TP11: 24V-TP-H; TestPoint_THTPad_D1.0mm_Drill0.5mm
U3: AMS1117-3.3; SOT-223-3_TabPin2; LCSC C6186
U4, U5: ID_LM66100DCKR; SC-70-6; LCSC C2869734
U9: DMP4065S-7; SOT-23; LCSC C182476

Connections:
5V_USB: C14.1, R29.1, U3.3 (VI); also elsewhere on the board
24V_SENSE: R30.2, R32.2; also elsewhere on the board
+3V3: C15.1, C16.1, C17.1, R7.2, TP2.1, U4.3 (*CE), U4.6 (VOUT), U5.3 (*CE), U5.6 (VOUT); also elsewhere on the board
+5V: C10.1, J2.A4 (5.0V_A), J2.A5 (5.0V_A), R9.2, TP4.1; also elsewhere on the board
+24V: F1.1, R8.2, R30.1, R37.2, TP3.1, TP11.1, U9.2 (S); also elsewhere on the board
+24V_BP: C9.1, F1.2, J2.A17 (24V_A), J2.A18 (24V_A)
/Power Circuitry/3V3_BP: C11.2, J2.A1 (3.3V_A), J2.A2 (3.3V_A), TP6.1, U4.1 (VIN)
/Power Circuitry/3V3_USB: C5.1, C12.1, TP9.1, U3.2 (VO), U5.1 (VIN)
CAN_N: J2.B13 (CAN_L); also elsewhere on the board
CAN_P: J2.B14 (CAN_H); also elsewhere on the board
GND: C5.2, C8.2, C9.2, C10.2, C11.1, C12.2, C14.2, C15.2, C16.2, C17.2, C24.2, D5.1 (K), D6.1 (K), D7.1 (K), D8.1 (K), J2.A3 (GND_A), J2.A6 (GND_A), J2.B4 (GND_A), J2.B5 (GND_A), J2.B6 (GND_A), Q5.2 (S), R32.1, R38.1, TP5.1, TP7.1, U3.1 (ADJ), U4.2 (GND), U4.5 (ST), U5.2 (GND), U5.5 (ST); also elsewhere on the board
unnamed: D5.2 (A), R7.1
unnamed: D6.2 (A), R8.1
unnamed: D7.2 (A), R9.1
unnamed: D8.2 (A), R29.2
unnamed: Q5.3 (D), R23.1
unnamed: Q5.1 (G), R38.2, R39.2
unnamed: C8.1, FB1.1, U9.3 (D)
unnamed: R23.2, R37.1, U9.1 (G)
VPT: C24.1, FB1.2; also elsewhere on the board
VPT_EN: R39.1; also elsewhere on the board

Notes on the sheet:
Power Input (Stack Backplane)
24V-LED: Vf=2.6, R=4.7k, I=4.5mA
3V3-LED: Vf=2.6, R=150, I=4.7mA
Power MUX (Dual ORing)
5V-LED: Vf=2.6, R=510, I=4.7mA
VPT Switching
Power Ouputs
Power LED Calculations
PI-filter for filtering
USB VBUS Regulation (->3V3)

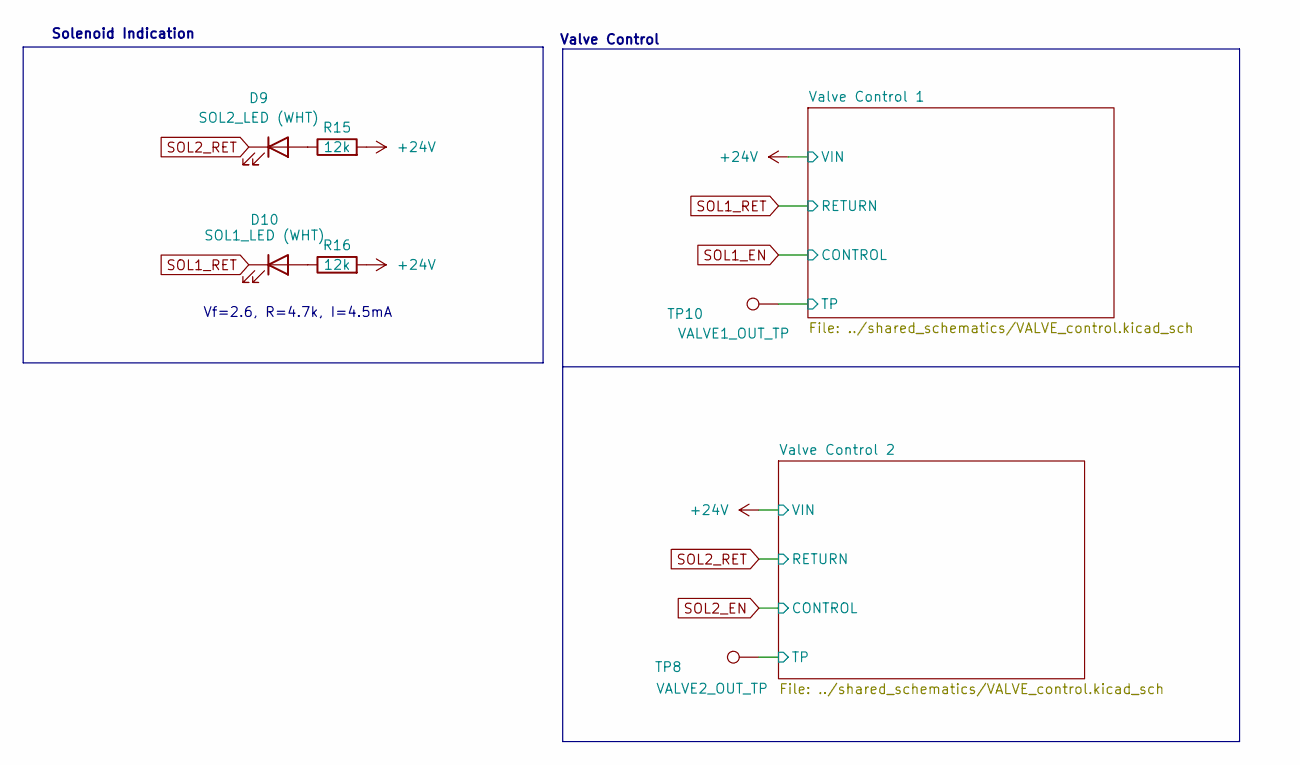
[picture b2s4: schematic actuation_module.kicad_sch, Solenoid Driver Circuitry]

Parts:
D9: SOL2_LED (WHT); LED_0603_1608Metric; LCSC C2290
D10: SOL1_LED (WHT); LED_0603_1608Metric; LCSC C2290
R15, R16: 12k; R_0603_1608Metric; LCSC C22790
TP8: VALVE2_OUT_TP; TestPoint_Pad_1.5x1.5mm
TP10: VALVE1_OUT_TP; TestPoint_Pad_1.5x1.5mm

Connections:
+24V: R15.2, R16.2; also elsewhere on the board
unnamed: D9.2 (A), R15.1
unnamed: D10.2 (A), R16.1
SOL1_RET: D10.1 (K), TP10.1; also elsewhere on the board
SOL2_RET: D9.1 (K), TP8.1; also elsewhere on the board

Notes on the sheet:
Valve Control
Vf=2.6, R=4.7k, I=4.5mA
Solenoid Indication
